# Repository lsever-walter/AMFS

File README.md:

# Active Magnetic Field Stabilization
Our goal is to generate magnetic fields on the order of 3 Gauss and to stabilize these magnetic fields to within a signal-noise ratio of $10^3$ for longterm drift (over the course of hours to days) and for 60Hz harmonic noise. This magnetic field stabilization scheme will improve stability for experiments that rely on (near) constant magnetic fields.

## Table of Contents
- [Motivation](#Motivation)
  - [Zeeman Sublevels and Fine Structure](#Zeeman-Sublevels-and-Fine-Structure)
  - [Zeeman Effect](#The-Zeeman-Effect)
- [Components List](#Components-List)
- [Schematics and Components](#Schematics-and-Components)
  - [Experimental Setup](#Experimental-Setup)
  - [Moku Go](#Moku-Go)
  - [N Channel MOSFET](#N-Channel-Mosfet)
  - [Helmholtz Coils](#Helmholtz-Coils)
  - [Magnetometer](#Magnetometer)
- [Feedback Control](#Feedback-Control)
  - [PID Controller](#PID-Controller-(Moku-Go))
  - [Tuning Controller](#Tuning-Controller)
- [Feedforward Control](#Feedforward-Control)
  - [Line Triggering](#Line-Triggering)
  - [60Hz Harmonic Cancellation](#60Hz-Harmonic-Cancellation)
- [Combined Feedback Feedforward Control](#Feedback-and-Feedforward)
- [Two Probe Stabilization with Qnimble and LNA](#Two-Probe-Stabilization-with-Qnimble-and-LNA)
  - [Two Probe Setup Guide](#Two-Probe-Stabilization-Setup-Guide)
  - [Two Probe Data](#Two-Probe-Stabilization-Data)
- [Future Work](#Future-Work)
- [Repository File Structure](#Repository-File-Structure)
- [Contributors](#Contributors)

# Motivation

## Zeeman Sublevels and Fine Structure
<div align="center">

</div>

In many physics groups investigating the interaction between light and matter use single, or few, atoms confined to a "trapping region." Lasers can drive electronic transitions between energy or angular momentum levels in atoms to investigate their internal structure and to run atomic clock and quantum logic experiments. Pictured above is the level structure of a Strontium 87 ion whose different orbitals experience further splittings for slight changes in the transition frequency which are called "Zeeman Sublevels." Often, exciting transitions between particular Zeeman sublevels is advantageous for certain experiments due to the long lifetimes of the excited state and narrow laser frequencies required to drive the transtion.

## The Zeeman Effect

Unfortunately, ambient magnetic fields in the laboratory can shift the Zeeman Sublevels of an atom during the course of an experiment causing a loss in precision and failure of an experiment. Therefore, to run many atomic and molecular optics, or AMO, experiments it is vital to stabilize the magnetic field experienced by the confined atoms or molecules against ambient magnetic field noise. The goal of our project was to generate and stabilize a 3 Guass magnetic field against slow and fast magnetic field drift as well as the 60Hz harmonics from the mains electricity.

# Components List

1. [MOKU:Go](https://www.mouser.com/ProductDetail/Liquid-Instruments/MOKUGO-M2-WHITE?qs=XAiT9M5g4x%2FfNk%2F%252BrYDr5A%3D%3D&mgh=1&gclid=CjwKCAjw-IWkBhBTEiwA2exyO_NAC4Yzw-N6Kk_8Ar5idSuqgZzDE3XjnfIC7eEdjNcVtmOxlln81RoCZbEQAvD_BwE) - Microcontroller to act as Oscilloscope, PID loop, and AWG
2. [MOSFET N Channel](https://media.digikey.com/pdf/Data%20Sheets/ST%20Microelectronics%20PDFS/2N7000,%202N7002.pdf) - Transistor with input pin, and sends current from drain to source pins
3. [OPAMP LM358AP](https://www.digikey.com/en/products/detail/texas-instruments/LM358AP/379836?utm_adgroup=Texas%20Instruments&utm_source=google&utm_medium=cpc&utm_campaign=PMax%20Shopping_Supplier_Texas%20Instruments&utm_term=&utm_content=Texas%20Instruments&gclid=CjwKCAjw-IWkBhBTEiwA2exyO5folY13R_LqYqakT_OlBMVobZKeyYGEDrK9Rew3klFTzHKU20AtqRoCejcQAvD_BwE) - Low Noise OP AMP 
4. [Bartington Magnetometer](https://www.bartington.com/products/high-performance-magnetometers/mag-03-three-axis/) - reads magnetic field 0-10G, 3kHz bandwidth 
5. [Oscilloscope DS1064](https://www.tequipment.net/RigolDS1064B.html) - with option to AC line trigger

# Schematics and Components

## Experimental Setup

<div align="center">

</div>

Our Experimental Setup consists of two coils which produce the Helmholtz Field at the center (in our case, 3G). The magnetometer is placed at the center of the coils, and the voltage reading is sent to the Moku:Go controller. The controller is connected to a laptop on which we use the Moku software to run the PID loop and control its parameters. The PID loop output error signal is sent to the first shunt transistor on the bread board (see [Future Work](#Future-Work) for our plans to optimize the circuit on a pcb), "MG Out1" in the diagram above, that shunts current from the coils to alter the magnetic field. Simulatenously, an oscilloscope is used to line trigger a TTL signal on the 60Hz AC line from the wall outlet which is input to the Moku:Go and is used to trigger the Moku:Go Arbitrary Waveform Generator (AWG). The AWG signal is sent to the second shunt transistor, "MG Out2", which is used for feedforward.

## Moku Go
<div align="center">

</div>

The Moku:Go is a multi-instrument controller that has high sensitivty, sample rate, and output rate which made it ideal to use for this project. The Moku:Go acted as an oscilloscope for the voltage readings from our magnetometer and processed those readings in its PID Controller that was used to generate the feedback error signal. The Moku:Go also had a built in Artbitrary Wave Form generator with which linear combinations of sin waves of different frequencies, amplitudes, and phases could be output and with which feedforward was accomplished. All of our data was also logged using the Moku:Go data logger instrument which has high sample rate and resolution. The Moku:Go power supplies were not used since constant current mode could not be reliably achieved to output .5A to our coil circuit since the impedence of the circuit exceded 5V.

## N Channel Mosfet
<div align="center">

</div>

We used an N Channel Depletion Type MOSFET as our shunt transistor to control the current flow through the coils. The MOSFET is a "Metal Oxide Semiconductor Field Effect Transistor" which  changes its resistance been its source and drain pins in response to an applied voltage to its gate pin. The MOSFET(s) were placed in parallel with the coils and the error signal from the Moku:Go was output to their drains to modulate their resistance and consequently the current passing through the coils to do feedback and feedforward control.

## Helmholtz Coils
<div align="center">

</div>

Coils in a Helmholtz Configuration were used for this project due to the stability of the magnetic field in the center of the coils. The coils were placed in series so that the magnetic field pointed in the same direction along the quantization axes parallel to the magnetometer and perpendicular to the plane of the coils with a magnitude $B=(\frac{4}{5})\frac{\mu_{0}NI}{a}$. The resistance of the coils used was on the order of $.3\Omega$ which meant that driving a total current of .25A through our circuit and >.1A through the coils resulted in a 3G magnetic field.

## Magnetometer
<div align="center">

</div>

The magnetometer used in this project was a Bartington Mag-03 fluxgate magnetometer that had a sensor bandwidth of 3kHz and a measuring range of .7 to 10G. The sensor noise floor is <6pTrms per $\sqrt{Hz}$ at 1Hz and offered excellent resolution required for precise PID feedback control. The magnetometer output a voltage signal with a 1:1 ration between volts and gauss to the Moku:Go which applied the PID controller to it. In the future, this magnetometer's ability to sense along three sepperate axes could allow for active magnetic field stabilization along three quantization axes or to sense a magnetic field gradient along one axes. 

# Feedback Control

Our feedback loop consists of a magnetometer, a PID loop in MOKU:Go, and a MOSFET in parallel to the coils shunting current to ground to modulate the field. 

The Bartington Magnetometer is placed at the center of the coils, and sends its reading to the first input pin of the MOKU:Go. The voltage to field ratio of the magnetometer is 1V/G. This is sent to the MOKU's PID loop, where we varied the P and I parameters to reduce the standard deviation as much as possible. The D term was not used as this ended up saturating the PID loop once the external magnetic field became too high. We tuned the parameters to optimize for long term drift cancellation, so Feedforward could handle the faster moving deviations. 

The output of the PID loop was a signal that we sent into a Non-Inverting Amplifier, then to the MOSFET in parallel with our coils. 

The NonInverting Amplifier circuit consisted of an OpAmp, two resistors, and a capacitor. The circuit is below, and the gain of this circuit is 6. The purpose of this circuit is to set the input of the MOSFET in the middle of its range of 0-60 volts. We would then have more control on how much it attenuates the signal. 

<image src="https://github.com/lsever-walter/AMFS/assets/125600843/0734a2d0-c5d2-4a97-9a83-c12c311680be">
 
The output of this circuit was sent to the MOSFET to shunt current accordingly to ground.

## Tuning Controller
<div align="center">

</div>
When the PID feedback was off, there were significant noises in our magnetic field signal that were mostly composed of 60 Hz harmonics. As the feedback was enabled, the standard deviation decreased from 3.9 mG to 0.8 mG. We observed a distinct attenuation of power in small frequencies range of our FFT plot. However, there still remained 60 Hz harmonics peaks that are slightly reduced by PID feedback. By integrating the power spectral density over frequencies from 0 to 300 Hz, above which the PID feedback ceases to effect, we obtained an area ratio of 163.

# Feedforward Control

Feedforward control consists of modifying the input to the system by modulating the source of the disturbance. In this case, the disturbance is the 60Hz from the powerwall that leaks through the DC power supply, as well as 60Hz that enters the magnetic field from laptops and other devices that run at 60Hz. 

Our feedforward methology relies on finding the phase of the 60Hz sin wave in the magnetometer and shunting current to decrease the amplitude of this singal.

## Line Triggering

We AC line triggered from DS1064 Oscilloscope, and produced a TTL (time-to-live) at this frequency and sent this to the Moku:Go. The Moku's AWG produced a sin wave at this frequency. We set the period of this sin wave to be slightly more than 60Hz (~60.05 Hz), so that any error in the TTL's phase did not affect the AWG's produced sin wave.

We then obtained the signal from the magnetometer, and sent this into the MOKU:Go in multi instrument mode. We then phase shifted the sin wave produced by the Moku to be in phase with the 60Hz wave in the magnetometer reading. We then sent the in phase sin wave from the AWG to the second MOSFET in our circuit to shunt away current at this frequency to attenuate 60Hz in the magnetic field.

As a result, the 60Hz in the magnetic field was attenuated. 

## 60Hz Harmonic Cancellation
<div align="center">

</div>
The power spectral densities over frequency corresponding to cases of feedforward on and feedforward off are nearly identical, as what we have expected. This is because we were outputing a 60 Hz sinusoidal wave that is in phase with the magnetometer signals, the rest of the spectrum should, therefore, be highly similar. As we zoomed into the region of interest (f = 60 Hz), we observed an approximaely 8 dB attenuation at 60 Hz by subtracting the peaks to their respective noise floors, which are about the same in this case. 

# Feedback and Feedforward
<div align="center">

</div>
After the individual implmentation of PID feedback and mains electricity feedforward, we combined both methods to further attenuate the noises in our signal. The standard deviation was reduced to 0.4 mG, as contrast to 0.8 mG for PID feedback alone. There was about 35 dB attenuation of power spectral density at 60 Hz, from which we obtained by subtracting the peak value at 60 Hz from their respective noise floors. Through integrating the power spectral density to the bandwidths of PID feedback alone (f = 300 Hz) and of Feedback and Feedforward (f = 850 Hz), we calculated area ratios of 705 and 65, respectively.

# Two Probe Stabilization with Qnimble and LNA

## Two Probe Stabilization Setup Guide
1. The moku:go will be used for live measurements so you can tune things more quickly, the Qnimble is what’s actually used as the PID controller. 

2. Two BNC connectors go from the two magnetometer output ports that are being used to the LNA setup with the breadboard. Each BNC coming from the magnetometer should have a BNC to banana adapter on the end. The grounds of the banana adapters should be connected. The positive side of the banana adapters should go into the breadboard’s banana connector slots, one into the breadboard’s ground (green female end banana connector on the breadboard) and one into the breadboard’s Vb (black female end banana connector on the breadboard). 
3. Current then travels through those two ports and then each through its own 10k resistor. After current passes through each respective 10k resistor, there is a junction that then goes to the breadboard’s Va (red female end banana connector on the breadboard). 
4. The LNA’s input port should have a BNC to banana adapter on it, and you should put a banana cable (preferably red) from the breadboard’s Va connector to the positive terminal of the LNA. There should be another banana cable (preferably black) going from the ground of the magnetometer signals (it doesn’t matter which you connect it to since they should be connected to each other already)
5. The output of the LNA is split with one end into the moku’s input and one into the Qnimble’s input.
6. The LNA is a current amplifier, but we want to amplify a voltage, so we put resistors out front. It should be such that the resistors are quite high because we don’t the magnetometers to have to output much current at all. V=IR tells us that the current read will be I=V/R, so with 10k resistors like I’ve used, the current read by the LNA will be 1e-4 in amps of the voltage going in. For example if I supplied one volt, I would have 100uA being read by the LNA. Because I have two ~1V signals (for a 1 gauss field read by each probe) coming in from each magnetometer output, they will each turn into 100uA of current, and by the junction rule that current adds to 200uA when it goes into the LNA input, so it will read 200uA. There should be no concern about back flow of current because the LNA has very nearly zero resistance and the back flow path requires the current to flow through an extra 10k ohm of resistance, so the backflow current should be pretty much zero.
7. Because we have 10k resistors out front, set preamp to -200uA input offset. Be careful to make sure that you have the negative mode selected. Input offset depends on the resistors used, and -200uA is corresponds to zeroing the current of 2 signals each of 1V (for 1 gauss as read by each magnetometer probe) coming in. Have the preamp gain set to 100mA/V for tuning (this LATER gets increased to 200nA/V once you zero the center the fluctuating B field reading about 1G for each probe)
8. Turn on the op amp and circuit power supplies, OP Amp gets 20-30V, circuit pwr gets ~0.2A to start (you will vary this to get an LNA reading centered about zero). 
9. With the circuit pwr, the power supply needs to have its current limit set to output at a fixed current as opposed to a fixed voltage, so set that limit to 0.2A and that in the later steps to control the current. 
10. Turn on the LNA and view the LNA’s output in the moku:go desktop app with the Qnimble’s DAC offset set to ~0.4V.
11. Vary the circuit pwr current until the moku:go shows the signal as closely centered about zero as you can get, this means the field read by each magnetometer probe is 1G
12. Now increase the gain on the LNA to 10uA/V, repeat step 11 if the center of the signal changes from zero.
13. Now increase the gain once again to 1uA/V, again repeat step 11 if needed (best to get the signal as near as possible to centered about zero). You may also need to vary the DAC offset in the Qnimble applet for more fine tuning to get the LNA output centered about zero.
14. Now increase the gain on the LNA to the final level of 200nA/V and again tune the DAC offset to get it as nearly centered about zero as possible. 
15. Now it’s ready for testing the stabilization performance.
16. Note that this is very finely tuned for whatever setup you have it set to, so if you move a magnet within the vicinity or move a current carrying wire within the vicinity, you likely will have to re-calibrate by adjusting the DAC output offset in the Qnimble applet again.
17. Here are some parameters have performed well in tests:
P=0.0005, I=0.05, D=0, SP=0, DAC=0.414
The optimal DAC (DAC offset) value will probably differ, see the above setup guide for proper DAC tuning.

## Two Probe Stabilization Data

Note that this plot did not use feedforward or a direct attenuation of the 60Hz noise, this plot is only to showcase the ability to attenuate low frequency noise with the Qnimble Quarto as a controller, an SRS LNA to amplify the signal, and B field probes whose measurements are fed into a passive averager circuit to allow for two probe stabilization. This data was recorded for the PID parameters suggested in the setup guide. Many sets of parameters were tested, but this plot represents the most significant reduction in low frequency noise without significant overcorrection noise at higher frequencies. There is a small overcorrection hump that peaks at ~1kHz, but it is at roughly 1/1000 the noise levels of the low frequency noise that has been attenuated. 

# Future Work
For our future work we hope to implement the stabilization setup developed above on a linear paul trap. We hope to first move optimize our circuits with voltage regulators to protect the operation amplifiers and coils from DC current spikes that could damage the circuitry and potentially the magnetometer. We would then like to implement feedforward for further 60Hz harmonics to attenuate up to 240Hz which would likely increase our PID bandwidth as well. Finally, we would then aim to implement our setup on a linear paul trap by designing new coils to it the ion trap geometry and then use the ion itself to quantify the magnetic field stability in addition to, or perhaps instead of, the magnetometer. 

# Repository File Structure
  
All of the analysis and plotting of our data was done in python and the code used along with the plots included in this README are in the `AMFS/Analysis_code` subdirectory. The raw data is saved in CSV file format in the `AFMS/Data` subdirectory and can be used to reproduce or customize the included plots. The PCB schematics for the circuit board we want to use in the future have been included in the `AMFS/PCB Schematics` folder, however these were not used for this project and have not been tested. We have also included a pdf of our final presentation for this work in the `AFMS/Presentation` subdirectory. All schematics, photographs, and figures appearing in this README are stored in the `AMFS/Figures` folder. Finally, we included test scripts made public by liquid instruments to help with trouble shooting the Moku python API in the `AMFS/Controller` folder. This code was not used for this work but may be useful in the future should we want to switch to the Moku python API instead of the Moku Desktop App. 
  
# Contributors
This work was primarily done by Luka Sever-Walter, Xuanwei Liang, and Samyuktha Ramanan for 15CL at UCSB.

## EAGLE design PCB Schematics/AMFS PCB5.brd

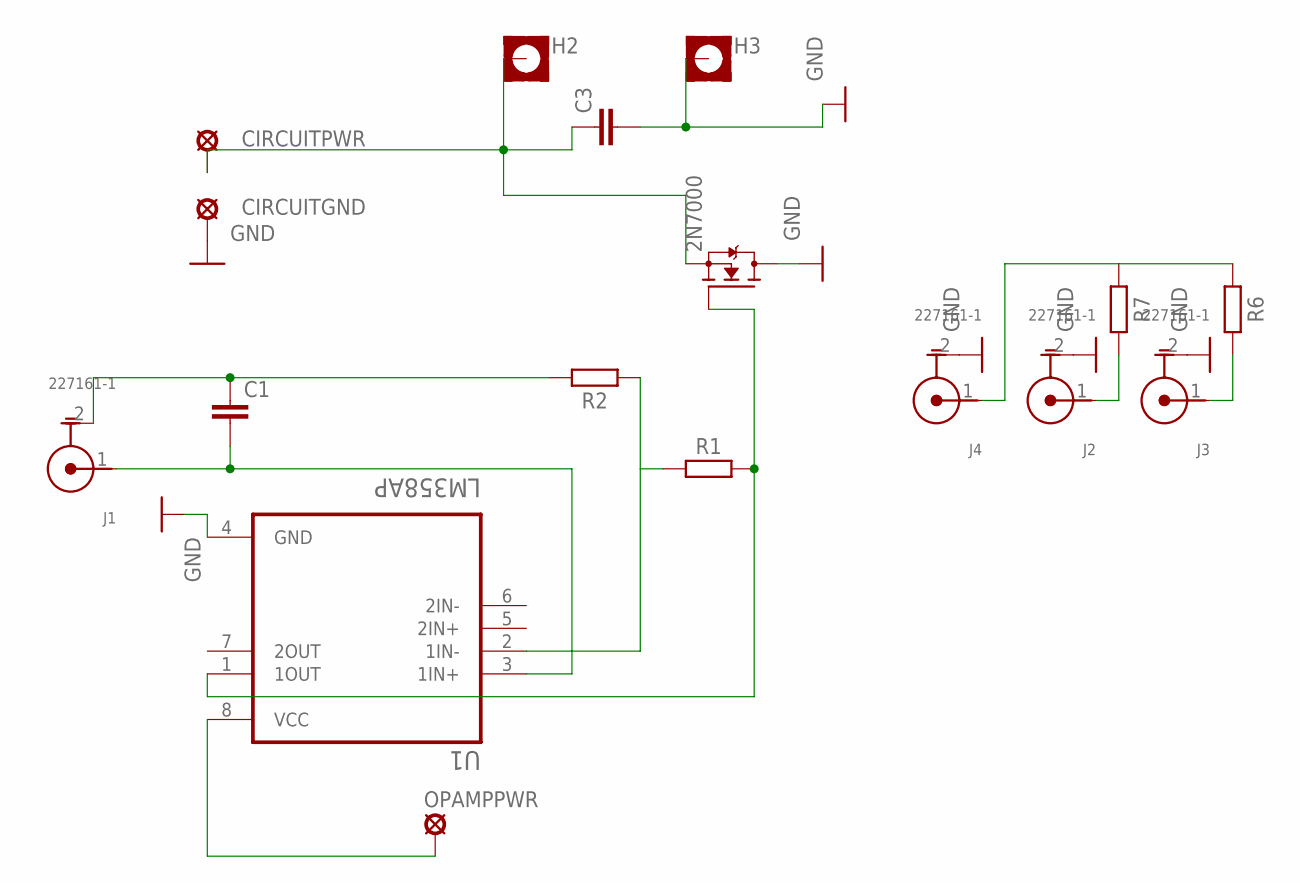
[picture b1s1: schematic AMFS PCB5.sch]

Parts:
C1, C3: C5/3.5; C5B3.5
CIRCUITGND: MCS10B
CIRCUITPWR: MCS10B
H2, H3: MOUNT-PAD-SQUARE2.8; 2,8-PAD-SQUARE
J1, J2, J3, J4: 227161-1; TE_227161-1
OPAMPPWR: LSP10
R1, R2, R6, R7: R_AXIAL-7.2MM-PITCH; RESAD724W46L381D178B
SHUNT: 2N7000; TO92-
U1: LM358AP; DIP794W45P254L959H508Q8

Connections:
GND: C3.2, CIRCUITGND.MP, H3.B2,8, J2.2 (G), J3.2 (G), J4.2 (G), SHUNT.1 (D), U1.4 (GND)
unnamed: C3.1, CIRCUITPWR.MP, H2.B2,8, SHUNT.3 (S)
unnamed: OPAMPPWR.MP, U1.8 (VCC)
unnamed: C1.2, J1.1 (C), U1.3 (1IN+)
unnamed: C1.1, J1.2 (G), R2.2
unnamed: R1.1, R2.1, U1.2 (1IN-)
unnamed: J2.1 (C), R7.2
unnamed: R1.2, SHUNT.2 (G), U1.1 (1OUT)
unnamed: J3.1 (C), R6.2
unnamed: J4.1 (C), R6.1, R7.1

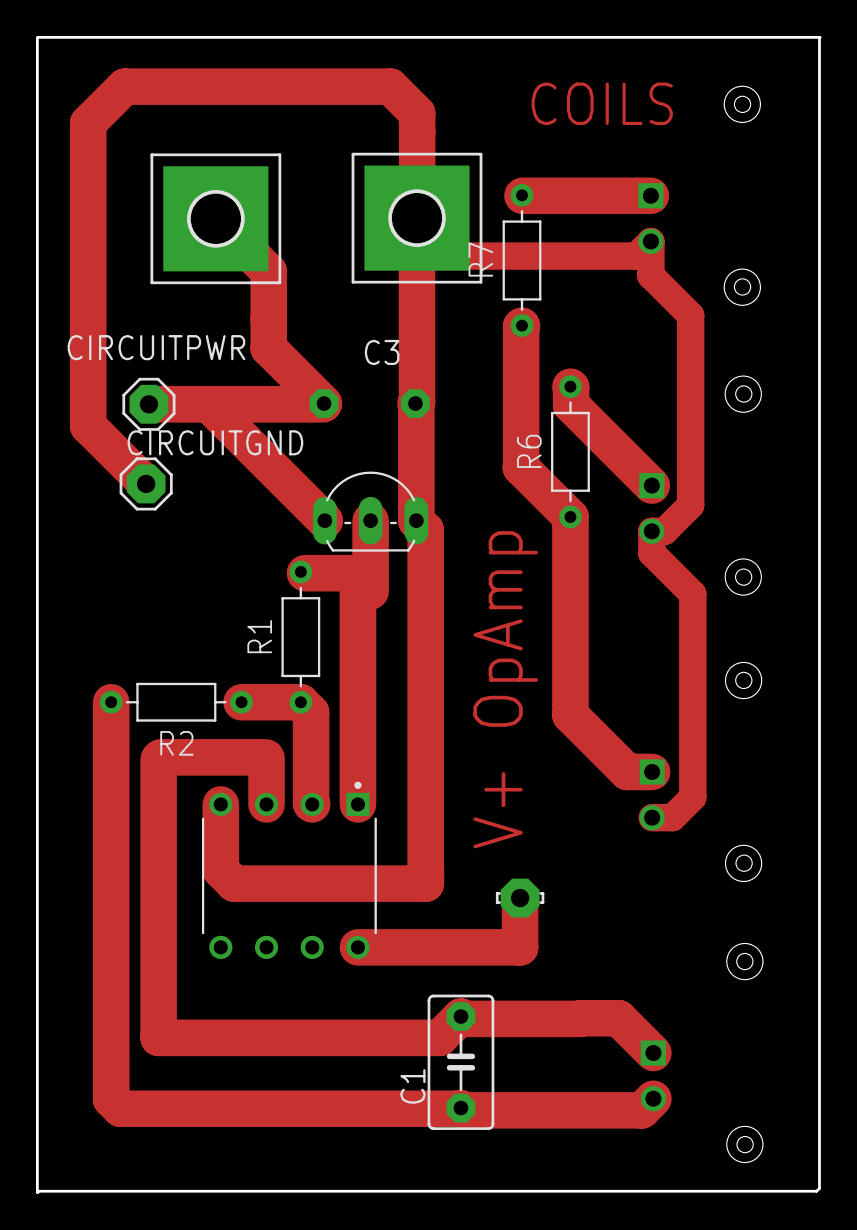
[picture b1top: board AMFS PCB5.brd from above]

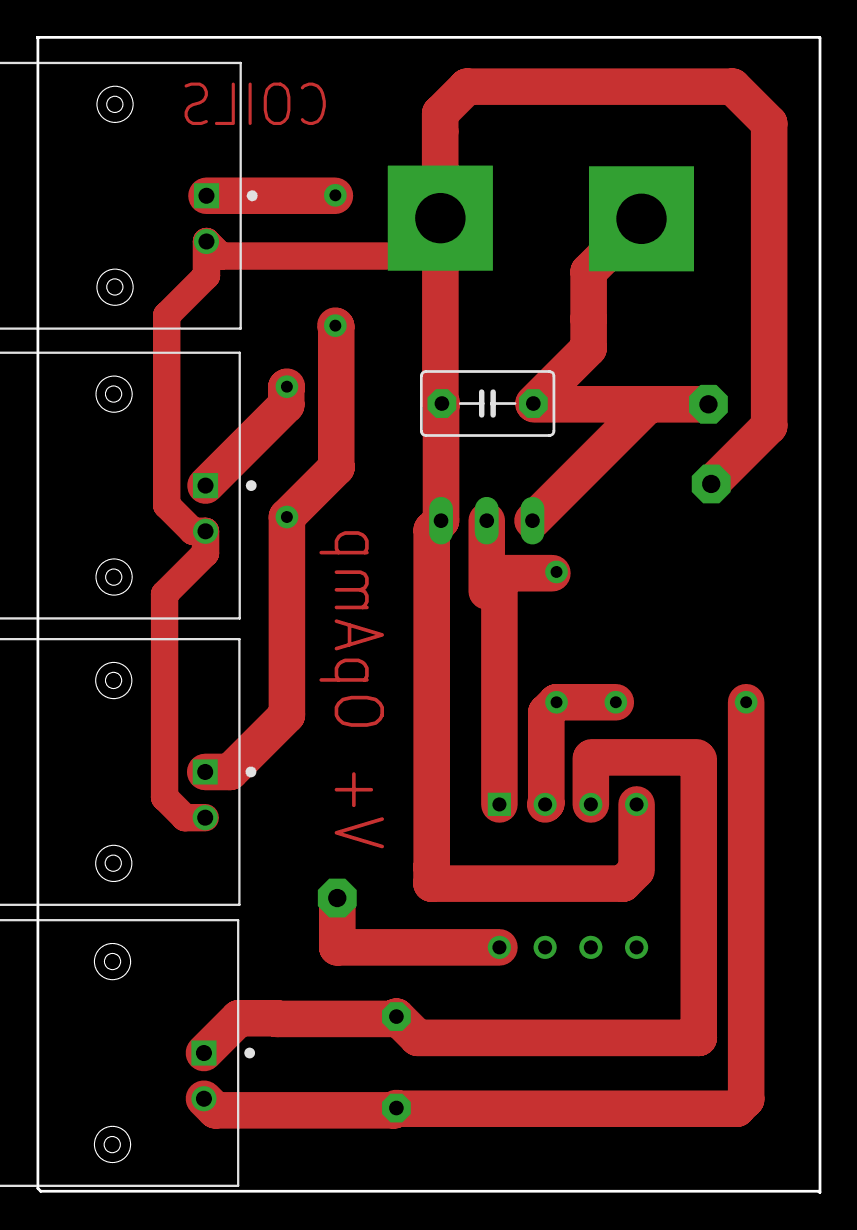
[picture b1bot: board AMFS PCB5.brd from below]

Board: 2 copper layers, 43.5 x 64.2 mm, 17 parts (5 on the bottom side), 10 nets.

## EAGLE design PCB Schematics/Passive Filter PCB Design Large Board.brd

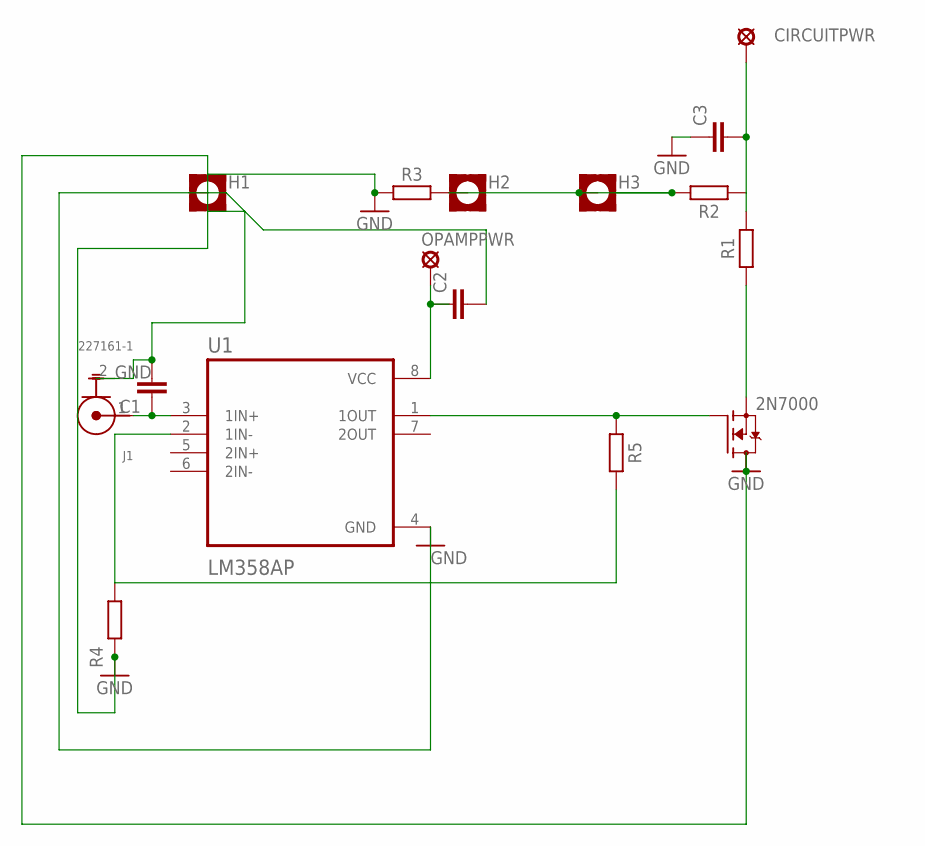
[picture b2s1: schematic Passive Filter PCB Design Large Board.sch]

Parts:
C1, C2, C3: C5/3.5; C5B3.5
CIRCUITPWR: MCS10B
H1, H2, H3: MOUNT-PAD-SQUARE2.8; 2,8-PAD-SQUARE
J1: 227161-1; TE_227161-1
OPAMPPWR: LSP10
R1, R2, R3, R4, R5: R_AXIAL-7.2MM-PITCH; RESAD724W46L381D178B
SHUNT: 2N7000; TO92-
U1: LM358AP; DIP794W45P254L959H508Q8

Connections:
GND: C1.2, C2.2, C3.1, H1.B2,8, J1.2 (G), R3.1, R4.2, SHUNT.1 (D), U1.4 (GND)
MOKU-IN: C1.1, J1.1 (C), U1.3 (1IN+)
unnamed: R1.1, SHUNT.3 (S)
unnamed: H2.B2,8, H3.B2,8, R2.1, R3.2
unnamed: C2.1, OPAMPPWR.MP, U1.8 (VCC)
unnamed: R5.1, SHUNT.2 (G), U1.1 (1OUT)
unnamed: R4.1, R5.2, U1.2 (1IN-)
V+30V: C3.2, CIRCUITPWR.MP, R1.2, R2.2

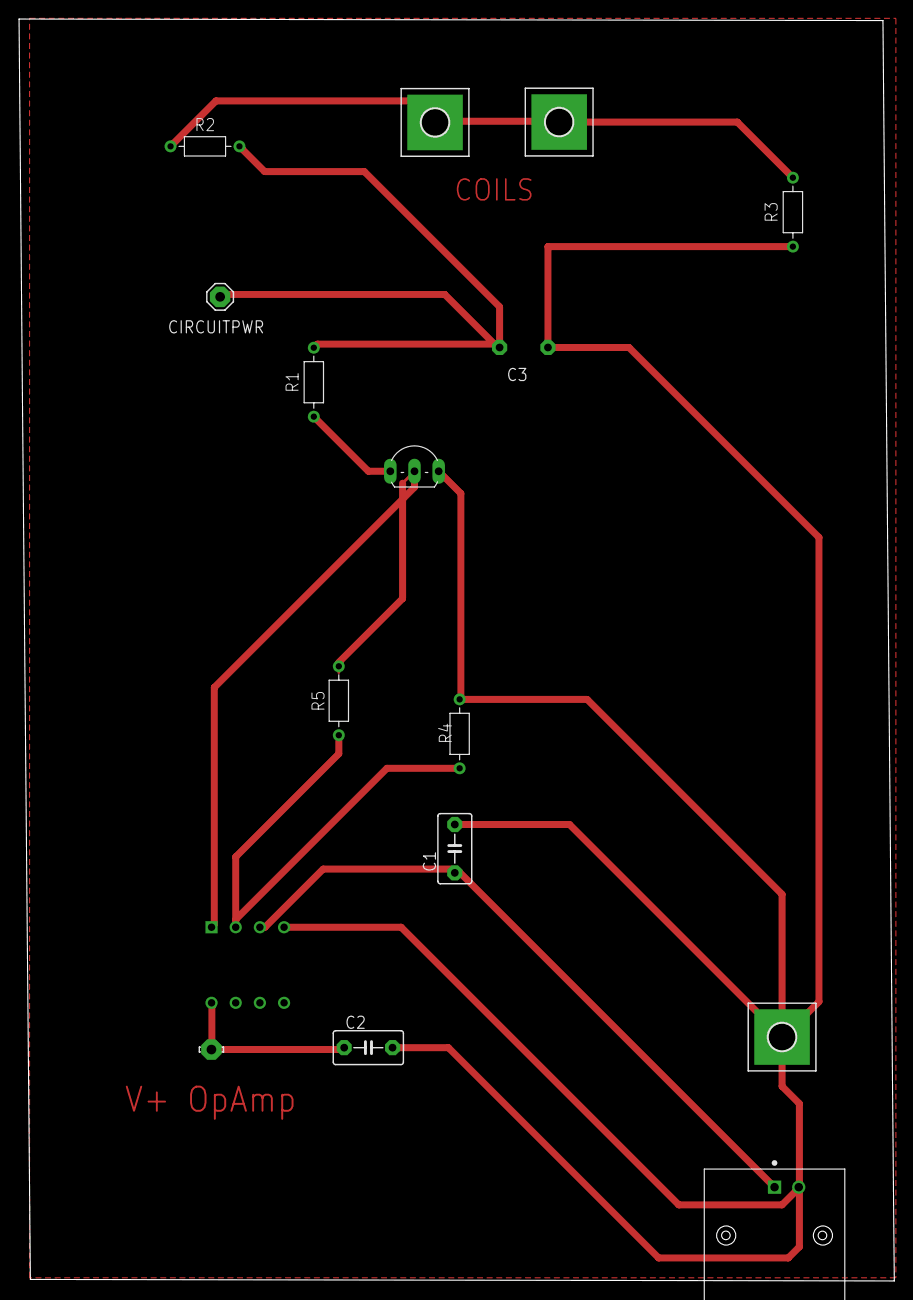
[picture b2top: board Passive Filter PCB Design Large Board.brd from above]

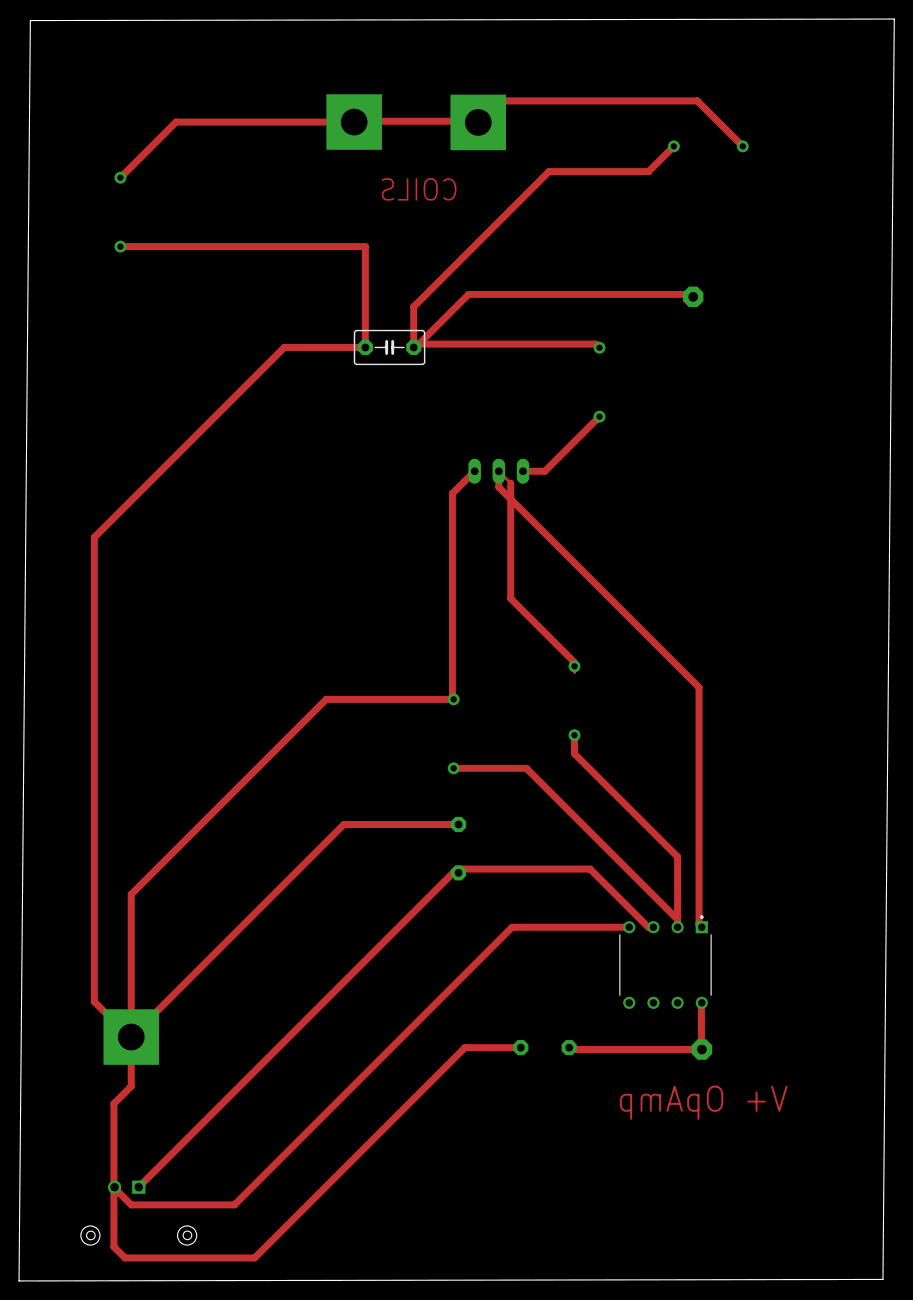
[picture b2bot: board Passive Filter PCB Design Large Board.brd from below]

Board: 2 copper layers, 91.9 x 132.6 mm, 16 parts (2 on the bottom side), 8 nets.

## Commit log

2023-04-09 Simple PID Code
2023-04-11 Adding Applet Generating Repo
2023-04-11 Applet Generator
2023-04-11 adding applet generator
2023-04-11 Delete .DS_Store
    redundant
2023-04-11 turning repo into module
2023-04-12 updating jax dependencies
2023-04-12 updating imports
2023-04-12 cleaning up
2023-04-12 Adding Plotter Applet
    Based it off of plot_pmt applet, need to continue refactoring it but off to a good start.
2023-04-14 updating connections
2023-04-14 testing MiM
2023-04-17 trouble shooting
2023-04-18 code for moku multi-instruments (Xuanwei Apr 17th)
2023-04-18 labjack plotter
2023-04-19 added unfinished real time plotting
2023-04-22 adding plots removing extra files
2023-04-24 updating analysis code
2023-05-01 adding bfield/fft plots
2023-05-04 BField Noise Data
2023-05-04 Updating BField Plots
2023-05-04 BField Raw Data
2023-05-04 Adding CSV files
2023-05-13 filter graphs
2023-05-14 Add files via upload
    Analysis codes and plots
2023-05-14 refactoring data
2023-05-14 updating plotter
2023-05-15 refactoring
2023-05-15 plots
2023-05-15 updating graphs
2023-05-16 Add files via upload
    Data analysis graphs
2023-05-16 Add files via upload
    update graph
2023-05-17 adding phase fitter
2023-05-21 updating plot/code
2023-05-22 updating pcb
2023-06-06 cleaning up main
2023-06-06 adding folders
2023-06-07 adding figs
2023-06-07 addings figs
2023-06-07 updating mosfet
2023-06-07 adding plots
2023-06-08 Create empty
2023-06-08 create a new folder Presentation
2023-06-08 Upload Presentation Slides
2023-06-09 Delete AMFS_circuit1.png
    Wrong sign for the battery
2024-03-28 Update README.md
    added setup guide for 2 probe stabilization with qnimble and LNA
2024-03-28 Most recent PCB files
    Flipped op amp, flipped BNCs, removed no longer useful resistors and a capacitor that didn't make much sense, and added LNA passive averaging circuit.
2024-03-28 Latest AMFS PCB
    Includes LNA passive averaging resistors and BNC connectors.
2024-04-01 Add files via upload
    Updated .brd file because it was previously missing the board layout and wouldn't open in the bantam software
